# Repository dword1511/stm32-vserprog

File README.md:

# stm32-vserprog:
## flashrom serprog programmer based on STM32 MCU & USB CDC protocol.
**This project deprecates previous [`serprog-stm32vcp`](https://github.com/dword1511/serprog-stm32vcp) project,
  which uses STMicro's proprietary firmware library. Most functions are the same.**

* * *
### Features
* Fully open-source: now with [`libopencm3`](https://github.com/libopencm3/libopencm3) instead of STMicro's proprietary firmware library.
* Affordable and simple hardware:
  * An _STM32F103C8T6_ MCU, an 8MHz crystal, a 3.3V _1117_ LDO, some _0805_ capacitors, resistors and LEDs
    along with dedicated PCB available on OSH Park ([V2](https://oshpark.com/shared_projects/08Rj6sSm)
    or [V3](https://oshpark.com/shared_projects/vKn08YZG))
  * Or some general-purpose _STM32_ development boards,
  just add a new header file under "boards" folder to assign correct GPIO for USB D+ pull-up (_STM32F1_ only) and LEDs.
  * Hardware USB 2.0 Full-Speed and efficient virtual COM port with USB CDC protocol operates at any baud rates,
  eliminates the need of USB-to-UART bridges and the headache that comes with them.
  * **Ironically, you will still have to buy or borrow a USB-to-UART bridge (not RS-232 but TTL level) to program the programmer itself,**
  unless you are using an _STM32F0x2_ device (which has USB ISP capability) or boards with embedded _ST-Link_ (see @FabianInostroza's fork).
* Hardware full-duplex SPI with DMA, multiple clock speeds available (default at the one closest to but under 10MHz), _e.g._ on STM32F103 targets:
  * 36MHz
  * 18MHz
  * 9MHz *(Default)*
  * 4.5MHz
  * 2.25MHz
  * 1.125MHz
  * 562.5kHz
  * 281.25kHz
* 2 status LEDs (controlled with 1 GPIO):
  * Busy is lit during operation (inverse for boards with only one LED).
  * Different operations cause different patterns of blinking:
  mostly busy = reading, both on = writing, flashing alternatively = erasing.
  * Busy blinks alone if a hard fault or NMI is detected. Please unplug and replug the programmer.
  If the situation persists, please consider [opening a new ticket](https://github.com/dword1511/stm32-vserprog/issues).
* `flashrom` "serprog" protocol:
  * Operates on all major platforms (see [`flashrom` wiki](http://www.flashrom.org/Flashrom)).
  * Driver-free on Linux. On Windows may require ST's VCP driver
  (or just hack the `.inf` file of other CDC drivers, not confirmed).
* Firmware is interrupt-free except for low-level USB handling -- robust, easy to debug and modify.
* Fast:
  * Read speed up to 850KiB/s @ 36MHz SPI operation.
  * Dumps an _EN25Q64_ in 11 seconds and programs in 85 seconds (including `flashrom`'s calibration time).
  * Way faster than many commercial _CH341_-based USB programmers, especially for reading.
* Supports 25 and 26 series SPI flash chips.
  **45 series flash chips have different pinouts. Thus for the V2 PCB mentioned above, you will need an adapter.**

* * *
### Installation
1. Install `stm32flash` and the `gcc-arm-none-eabi` toolchain.

  On Debian, simply do the following:

   ```bash
   sudo apt-get install stm32flash gcc-arm-none-eabi
   ```
  
  NOTE: some systems may require installing `newlib` (_e.g._ `libnewlib-arm-none-eabi`) manually. See [#27](https://github.com/dword1511/stm32-vserprog/issues/27).

1. Clone and compile.

  Simply type (change the board name accordingly, for details see the header of the `Makefile` or just type `make`):

   ```bash
   git clone --recurse-submodules https://github.com/dword1511/stm32-vserprog.git
   make BOARD=stm32-vserprog-v2
   ```
1. Program.

  Connect the USB-to-UART bridge to your computer first. Then connect _TXD_ and _RXD_ lines to your _STM32_ board with wires.
  On V2 or V3 boards mentioned above, connect _BOOT0_ (labeled _BT0_ on boards) to the 3.3V output of the USB-to-UART bridge.
  For other boards, find the _BOOT0_ jumper or ISP switch, put it into high or enabled.
  On some boards, you will also need to ensure _BOOT1_ is pulled low.
  Then, connect your _STM32_ board to your computer via USB to power it up.
  Finally, type:

   ```bash
   make BOARD=stm32-vserprog-v2 flash-uart
   ```
1. Done!

  Throw the USB-to-UART bridge away and enjoy.
  Do not forget to pull _BOOT0_ low before resetting or replugging the board.

* * *
### Usage
The following assumes Linux platform, and that the programmer appears as `/dev/ttyACM0`.

1. To read a flash chip:
  * Connect a 25 type SPI Flash to the board's DIP-8 slot or according to the schematics.
  * Connect your board to your PC via USB.
  * Type:

   ```bash
   flashrom -p serprog:dev=/dev/ttyACM0:4000000 -r file-to-save.bin
   ```
  * Sometimes `flashrom` will ask you to choose a chip, add something like:

   ```bash
   -c SST25VF040B
   ```
   This is because sometimes different devices with distinct timing requirements can only be distinguished by the device code,
   however currently `flashrom` will not read it as it is not returned by the `RDID` command.
1. To erase a flash chip:
  * Erase is automatically done during writing. However, if you simply want an empty chip, you will need to erase manually.
  * Type:

   ```bash
   flashrom -p serprog:dev=/dev/ttyACM0:4000000 -E
   ```
  * For certain chips like _MX25L6445E_, the first pass could fail with some old `flashrom` version,
    but if you try a second pass, everything will be alright. Seems that the first block needs more delay to be erased.
  * Flash contents are verified to be empty automatically.
  * The whole process can take a few minutes.
1. To write a flash chip:
  * Type:

   ```bash
   flashrom -p serprog:dev=/dev/ttyACM0:4000000 -w file-to-load.bin
   ```
  * Flash chips are checked and blocks that are not empty are automatically erased.
  * Images are verified after writing automatically.
  * The whole process can take a few minutes.

* * *
### Problems?
1. If you encountered something like "`Error: Cannot open serial port: Device or resource busy`", please try to stop or remove `ModemManager`.
1. Check your wirings and `flashrom` version. Do not forget to power the flash chip itself if operating on a breadboard or prototype board.
1. If you are sure it is caused by bugs in the programmer's firmware,
   please [open a new ticket](https://github.com/dword1511/stm32-vserprog/issues) and provide details,
   _e.g._ the board you are using and `flashrom`'s output. I appreciate your feedback.

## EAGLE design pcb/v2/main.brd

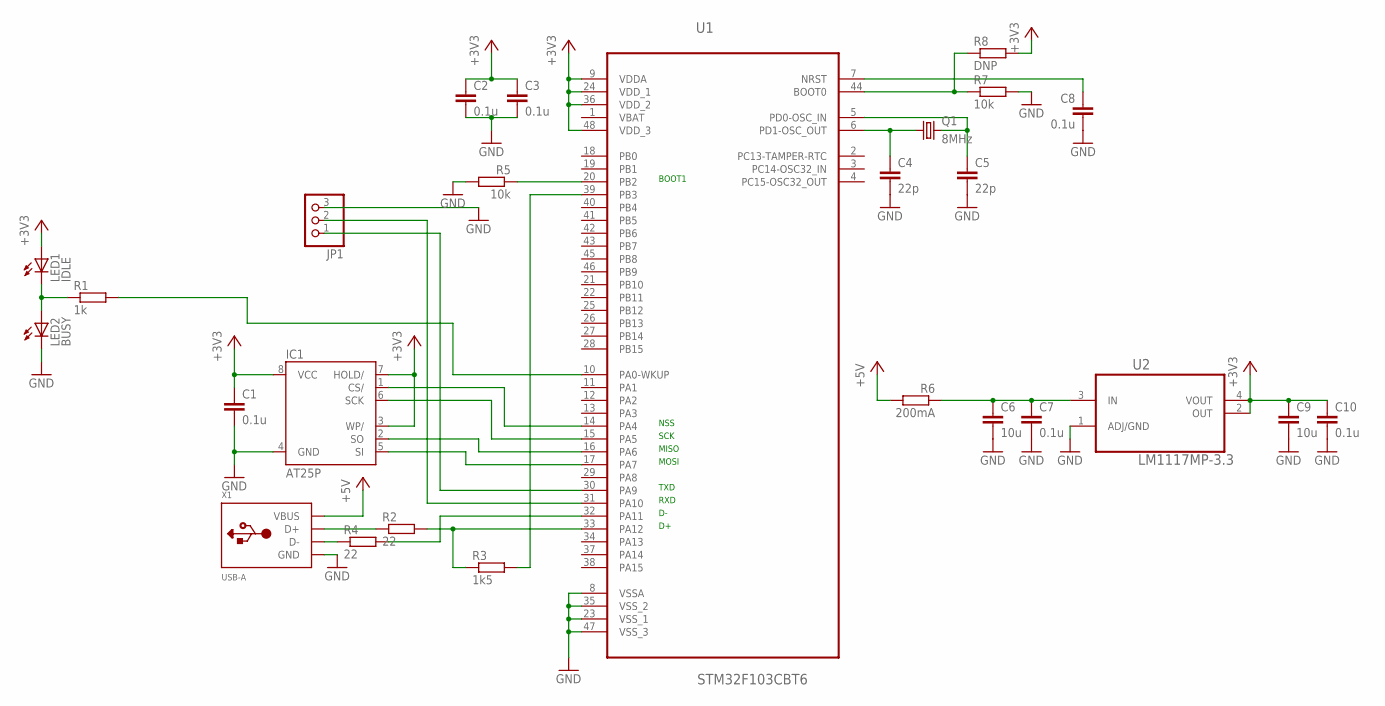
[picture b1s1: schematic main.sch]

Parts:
C1, C2, C3, C7, C8, C10: 0.1u; C0805K
C4, C5: 22p; C0805K
C6, C9: 10u; C0805K
IC1: AT25P; DIL08
JP1: PINHD-1X3; 1X03
LED1: IDLE; CHIP-LED0805
LED2: BUSY; CHIP-LED0805
Q1: 8MHz; HC49/S
R1: 1k; R0805
R2, R4: 22; R0805
R3: 1k5; R0805
R5, R7: 10k; R0805
R6: 200mA; R0805
R8: DNP; R0805
U1: STM32F103CBT6; QFP50P900X900X160-48N
U2: LM1117MP-3.3; SOT230P696X180-4N
X1: USB-A; MOLEX_480371000

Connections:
+3V3: C1.1, C2.1, C3.1, C9.1, C10.1, IC1.3 (WP/), IC1.7 (HOLD/), IC1.8 (VCC), LED1.A, R8.2, U1.9 (VDDA), U1.24 (VDD_1), U1.36 (VDD_2), U1.48 (VDD_3), U2.2 (OUT), U2.4 (VOUT)
+5V: R6.2, X1.1 (VBUS)
GND: C1.2, C2.2, C3.2, C4.2, C5.2, C6.2, C7.2, C8.2, C9.2, C10.2, IC1.4 (GND), JP1.3, LED2.C, R5.2, R7.2, U1.8 (VSSA), U1.23 (VSS_1), U1.35 (VSS_2), U1.47 (VSS_3), U2.1 (ADJ/GND), X1.4 (GND)
unnamed: C5.1, Q1.2, U1.5 (PD0-OSC_IN)
unnamed: C4.1, Q1.1, U1.6 (PD1-OSC_OUT)
unnamed: R5.1, U1.20 (PB2)
unnamed: R4.2, U1.32 (PA11)
unnamed: C8.1, U1.7 (NRST)
unnamed: R3.2, U1.39 (PB3)
unnamed: C6.1, C7.1, R6.1, U2.3 (IN)
unnamed: JP1.2, U1.31 (PA10)
unnamed: R7.1, R8.1, U1.44 (BOOT0)
unnamed: IC1.1 (CS/), U1.14 (PA4)
unnamed: IC1.6 (SCK), U1.15 (PA5)
unnamed: IC1.2 (SO), U1.16 (PA6)
unnamed: IC1.5 (SI), U1.17 (PA7)
unnamed: LED1.C, LED2.A, R1.1
unnamed: JP1.1, U1.30 (PA9)
unnamed: R4.1, X1.2 (D-)
unnamed: R2.1, X1.3 (D+)
unnamed: R1.2, U1.10 (PA0-WKUP)
unnamed: R2.2, R3.1, U1.33 (PA12)

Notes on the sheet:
TXD
RXD
BOOT1
NSS
SCK
MISO
MOSI

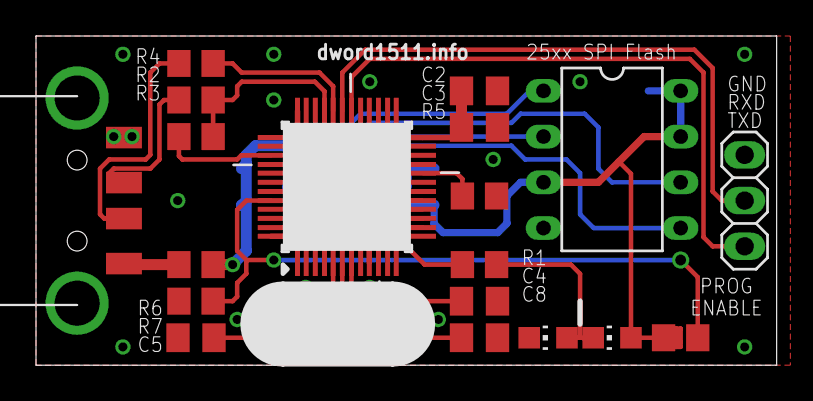
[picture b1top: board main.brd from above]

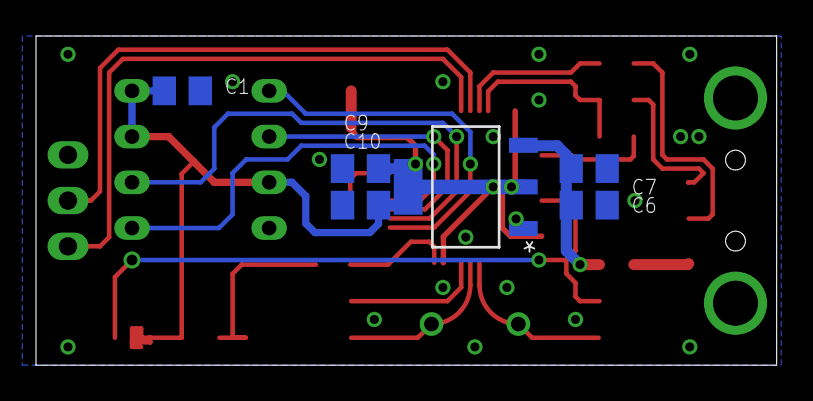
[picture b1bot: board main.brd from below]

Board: 2 copper layers, 41.1 x 18.3 mm, 26 parts (6 on the bottom side), 22 nets.

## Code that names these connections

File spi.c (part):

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static uint8_t dma_rxbuf[USBCDC_PKT_SIZE_DAT];

void spi_disable_pins(void) {
  /* Configure GPIOs: SS = PA4, SCK = PA5, MISO = PA6, MOSI = PA7 */
#ifdef STM32F0
  gpio_mode_setup(GPIO_BANK_SPI1, GPIO_MODE_INPUT, GPIO_PUPD_NONE, GPIO_SPI1_SCK | GPIO_SPI1_MOSI | GPIO_SPI1_MISO | GPIO_SPI1_NSS);
#else
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}

void spi_enable_pins(void) {
  /* Configure GPIOs: SS = PA4, SCK = PA5, MISO = PA6, MOSI = PA7 */
#ifdef STM32F0
  gpio_mode_setup(GPIO_BANK_SPI1, GPIO_MODE_AF, GPIO_PUPD_NONE, GPIO_SPI1_SCK | GPIO_SPI1_MOSI);
  gpio_mode_setup(GPIO_BANK_SPI1, GPIO_MODE_AF, GPIO_PUPD_PULLUP, GPIO_SPI1_MISO);
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
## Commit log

2015-11-29 project init
2015-11-29 added hardware files
2015-12-12 remove libfrser since we are not using AVR
2015-12-12 dummy version finished
2015-12-12 debug for protocol finished
2015-12-26 debug for direct-mode DMA read finished
2015-12-26 debug for direct-mode DMA write finished
2015-12-26 documents
2015-12-26 switch to GPLv3
2015-12-27 fix doc
2015-12-28 multi-board support
2015-12-28 added pcb version 3
2015-12-29 output 0xff when no chip connected
2016-01-22 prepare to support more targets
2016-01-23 more testing on GD32, SPI not working
2016-02-01 blinking more consistent across different target
2016-02-28 preliminary support for stm32f0x2. dma / spi is not working yet.
2016-03-03 enhanced makefile
2016-03-03 update readme slightly
2016-03-03 rename stm32-tiny042-v1 to stm32-tiny042 since 2 versions are equivalent
2016-03-03 SPI on STM32F0 fixed and tested
2016-06-09 make flashrom follow stable branch, since master does not exist
2016-06-29 fix Makefile
2016-07-02 Add support for 2 cheap ($2) STM32 Dev. boards called blue pill and red pill Since red one is no more manufactured or sold, board support name is stm32-bluepill You can build it with: make BOARD=stm3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
2016-07-02 Add symbolic link to stm32f103.mk for stm32-bluepill board
2016-07-02 add more information in board definitions, along with small fixes.
2016-07-02 misc. updates
2016-09-17 make flashrom follow the staging branch
    Apparently the flashrom repo receives some heavy refactoring.
    Building stm32-vserprog with the stable branch of flashrom doesn't work anymore, thus the change to staging.
2016-10-31 update submodules
2017-04-25 add parameters in sch
2017-05-23 remove prebuilt version since it does not make sense under new board selection system
2017-05-23 update submodules and tested. closes #11
2017-05-23 update the docs
2017-05-23 further update the docs
2017-05-23 add test/benchmark support
2017-05-23 fix CFLAGS
2017-06-26 specifiy gnu99 so libopencm3 works with gcc4
2017-06-26 switch to official flashrom git
2018-01-10 Update all submodules also switch flashrom remote to official repo and update to v1.0 stable tag while we are at it.
2018-04-01 Enable building on OSes that are not Linux.
    Use gmake command instead of make.
2018-07-17 update submodules and Makefile
2018-07-17 enable iwdg
2018-07-23 Add support for a cheap (~￥20) STM32 Dev. board The board is called JZ-01 V2.0, and can be bought from https://detail.tmall.com/item.htm?id=554703784397 , from which an RAR package containing schemat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
2018-07-23 split flash targets. In the future, board.mk will aliase flash to the correct target.
2018-09-12 Add option to clone submodules automatically
2018-09-12 Fix build warnings for unused functions
2018-09-28 Fix some typos
2018-09-28 Makefile: Allow building libopencm3 with a different cross-toolchain
2018-10-21 vserprog.c: Don't include <stdio.h>
    There's no need to include it.
2018-10-21 Add a Travis-CI script
    Travis-CI can automatically build-test the code on every commit or pull
    request.
2018-10-28 Adds command to enable/disable output buffers.
2018-11-09 fix oe for stm32f0
2018-11-19 Add note for newlib
2018-11-19 expected autolink... added link manually
2019-07-01 Upgrade flashrom to stable 1.1.x branch and libopencm3 submodules
2019-07-20 Add a new schematic and replace the IC base of the DIP-8 package with the lock seat of the ZIP-Socket-16Pin.
2019-07-21 replace ic base of dip-8 package to lock seat of zif-socket-16pin package
2019-08-02 update pcb version to v4
2019-08-04 adjustment details
2019-10-05 Add support for XTW100 flash programmer
    It's not functioning correctly yet. The USB device can be found in the
    OS, and the LED is on when running flashrom. However, it can only read
    a W25Q32.V correctly on the first run after the programmer plugs in,
    and cannot erase/write.
2020-02-29 Update Submodules - Flashrom bumped to v1.2.x stable branch
2020-02-29 Fix makefile see https://github.com/libopencm3/libopencm3/commit/7be50a5e75ed2d163d38a6759347c5e778ac02ab#diff-b67911656ef5d18c4ae36cb6741b7965
2020-05-01 Added support gitpod;
2020-05-01 Added support sr3;
2020-06-11 Revert "Add support for XTW100 flash programmer"
2020-09-30 Add XTW100 support
2021-03-22 Fix submodule link Update flashrom to 1.3.x branch Update libopencm3 to latest commit head
2021-03-22 Fix linking issues
2021-04-18 switch flashrom git url to mirror on GitHub
    The origin git host has moved to `https://review.coreboot.org/flashrom.git` .
    Officially mirrored on GitHub.
2021-08-18 add support for XTW2 and GD32F103
2021-08-18 flip BOARD_LED_HIGH_IS_BUSY for XTW2 (single-LED)
2021-08-18 update gd32f103.mk, missed a define
2021-10-13 Fix SPI baudrate for STM32F0 targets rcc.h provides a define for rcc_apb2_frequency which then collided with the local variable. As a result the SPI frequency was always 24MHz, no matter of the desir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
2021-10-13 Add definitions for an alternate board with a STM32F042
2022-07-28 Add support for a bluepill clone with the status LED inversed.
2023-01-15 bluepill: fix re-enumeration
2023-09-10 Add new board: Nucleo-F042K6
    Test setup:
    Nucleo-F042K6 wired to an EN25F80 (1024kB) on a breadboard.
    RESET/HOLD and WP pulled to VCC.
    flashrom -p serprog:dev=/dev/serprog1,spispeed=36M -w rand
    8,49s user 1,00s system 47% cpu 20,069 total
    flashrom -p serprog:dev=/dev/serprog1,spispeed=36M -v rand
2023-09-10 Set iInterface==serprog
    Now this and pico-serprog are both compatible an udev rule like:
    DRIVERS=="cdc_acm", ATTRS{interface}=="serprog", SYMLINK+="serprog%n"
